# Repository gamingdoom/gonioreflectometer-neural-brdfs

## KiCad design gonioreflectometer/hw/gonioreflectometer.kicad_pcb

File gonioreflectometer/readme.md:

BOM Link: https://docs.google.com/spreadsheets/d/1Ih6BdqQ3d26OCwwXPtMaEUR-iTpFJEZzmPmYw0t3Bok/edit?usp=sharing

Each board contains an RGB led with a TIR lens and a photo diode. They will be connected together in series.
Each board is able to disable/enable the next modules and the ability to program itself in order to facilitate this.

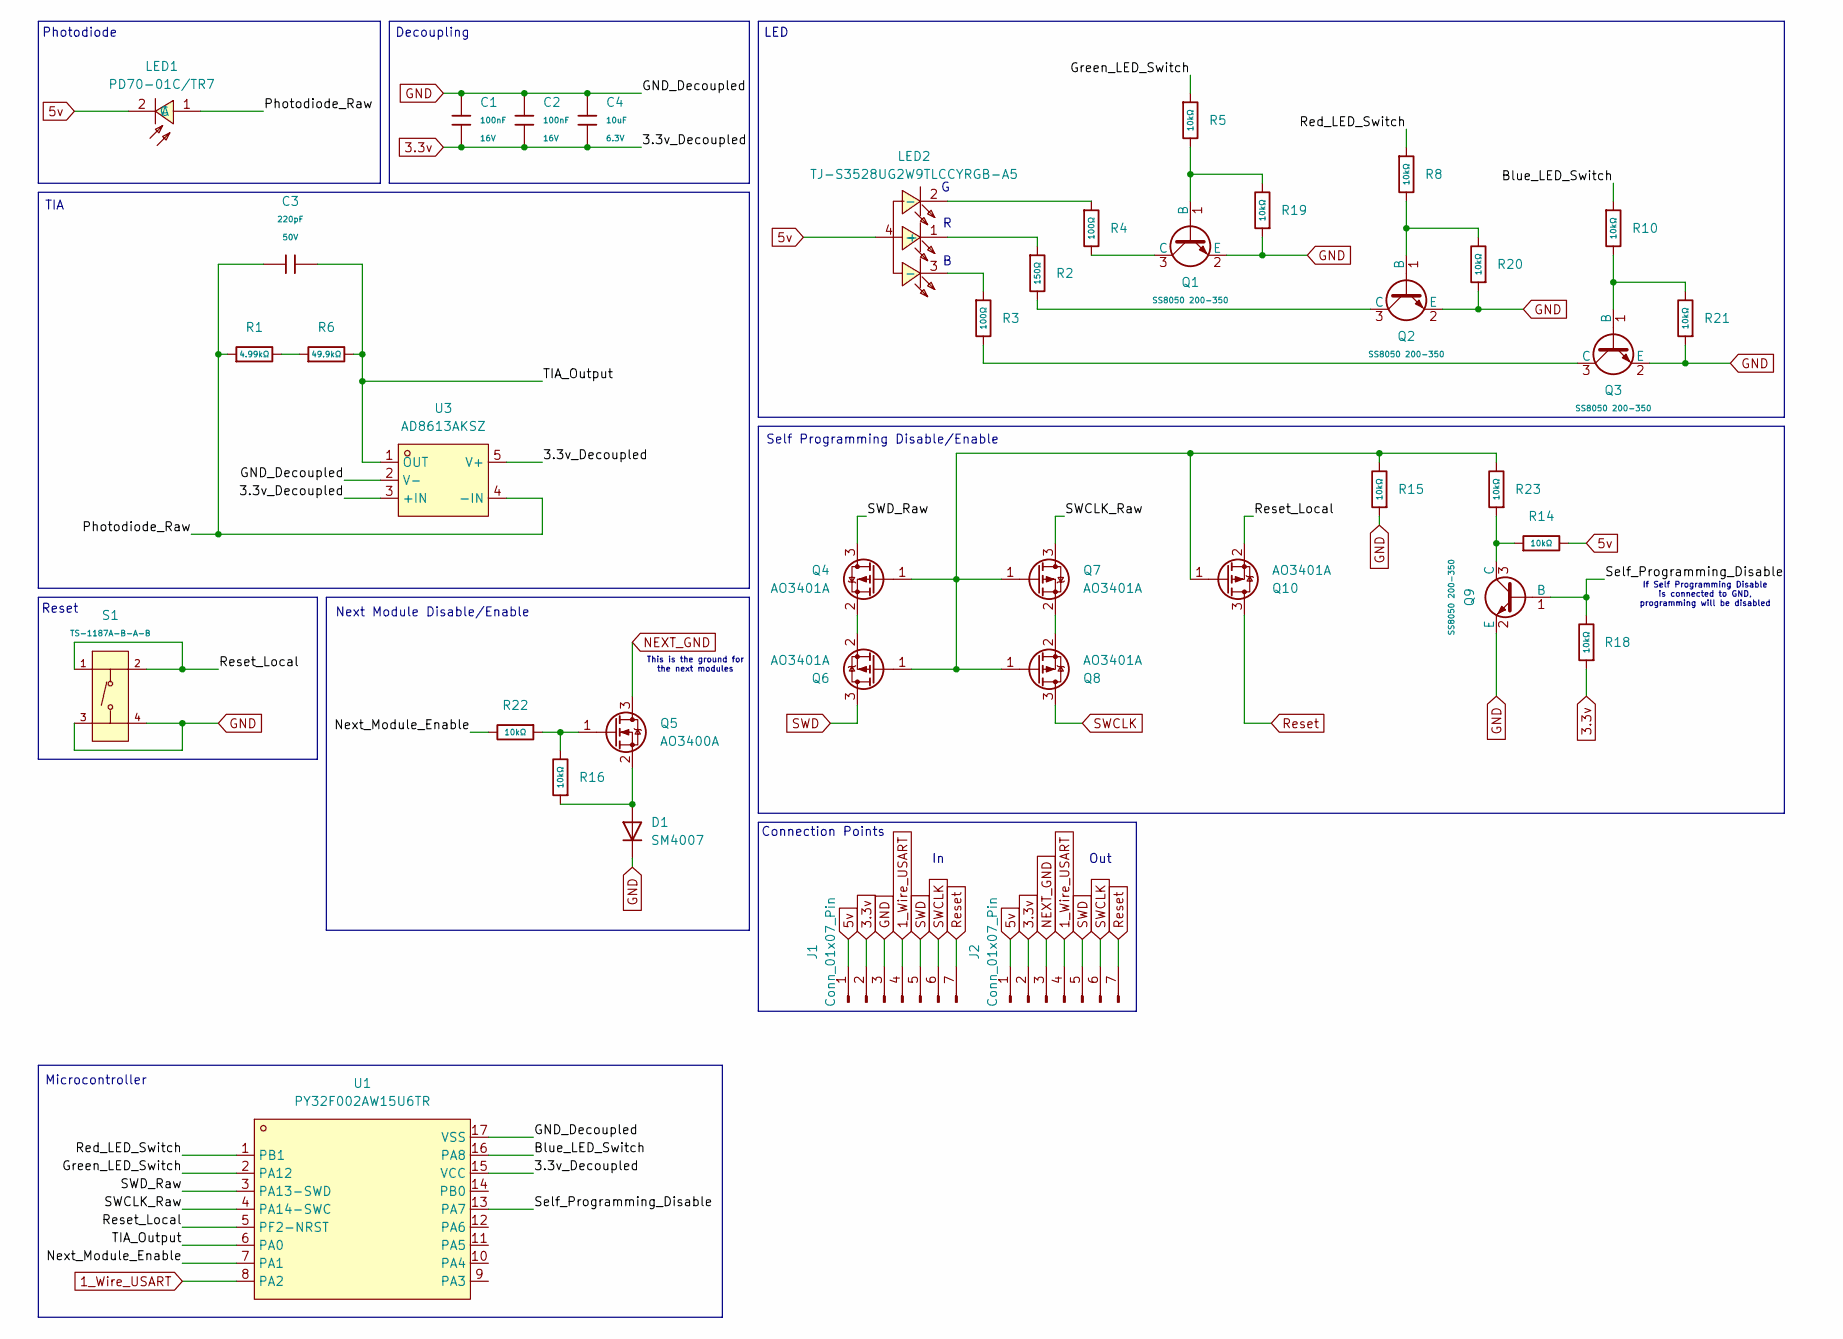
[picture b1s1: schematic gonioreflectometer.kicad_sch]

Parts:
C1, C2: 100nF; C_0402; Voltage Rated 16V; Tolerance ±10%; Part CL05B104KO5NNNC; LCSC C1525
C3: 220pF; C_0402; Voltage Rated 50V; Tolerance ±10%; Part 0402B221K500NT; LCSC C1530
C4: 10uF; C_0402; Voltage Rated 6.3V; Tolerance ±20%; Part CL05A106MQ5NUNC; LCSC C15525
D1: SM4007; D_MELF
J1, J2: Conn_01x07_Pin; PinHeader_1x07_P2.54mm_Vertical
LED1: PD70-01C/TR7; SENSOR-SMD_PD70-01C-TR7; MPN PD70-01C/TR7; LCSC Part C131196
LED2: TJ-S3528UG2W9TLCCYRGB-A5; LED-ARRAY-SMD_4P-L3.2-W2.7-TL-RD_TJ-S3528; MPN TJ-S3528UG2W9TLCCYRGB-A5; LCSC Part C601699
Q1, Q2, Q3, Q9: SS8050 200-350; Q_SOT-23; Part SS8050(RANGE:200-350); LCSC C2150
Q4, Q6, Q7, Q8, Q10: AO3401A; SOT-23
Q5: AO3400A; SOT-23
R1: 4.99kΩ; R_0603; Overload Voltage (Max) 75V; Tolerance ±1%; Part 0603WAF4991T5E; LCSC C23046
R2: 150Ω; R_0603; Overload Voltage (Max) 75V; Tolerance ±1%; Part 0603WAF1500T5E; LCSC C22808
R3, R4: 100Ω; R_0603; Overload Voltage (Max) 75V; Tolerance ±1%; Part 0603WAF1000T5E; LCSC C22775
R5, R8, R10, R14, R15, R16, R18, R19, R20, R21, R22, R23: 10kΩ; R_0402; Overload Voltage (Max) 50V; Tolerance ±1%; Part 0402WGF1002TCE; LCSC C25744
R6: 49.9kΩ; R_0603; Overload Voltage (Max) 75V; Tolerance ±1%; Part 0603WAF4992T5E; LCSC C23184
S1: TS-1187A-B-A-B; SW-SMD_4P-L5.1-W5.1-P3.70-LS6.5-TL-2; Voltage Rating (Dc) 12V; Part TS-1187A-B-A-B; LCSC C318884
U1: PY32F002AW15U6TR; TQFN-16_L3.0-W3.0-P0.50-BL-EP1.7; MPN PY32F002AW15U6TR; LCSC Part C5291740
U3: AD8613AKSZ; SC-70-5_L2.1-W1.3-P0.65-LS2.1-BR; MPN AD8613AKSZ(UMW); LCSC Part C22373372

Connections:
1_Wire_USART: J1.4, J2.4, U1.8 (PA2)
3.3v: C1.2, C2.2, C4.2, J1.2, J2.2, R18.1, U1.15 (VCC), U3.3 (+IN), U3.5 (V+)
5v: J1.1, J2.1, LED1.2 (C), LED2.4 (+), R14.2
/Blue_LED_Switch: R10.1, U1.16 (PA8)
/Green_LED_Switch: R5.1, U1.2 (PA12)
/Next_Module_Enable: R22.2, U1.7 (PA1)
/Photodiode_Raw: C3.1, LED1.1 (A), R1.1, U3.4 (-IN)
/Red_LED_Switch: R8.1, U1.1 (PB1)
/Reset_Local: Q10.2 (S), S1.1 (A), S1.2 (B), U1.5 (PF2-NRST)
/SWCLK_Raw: Q7.3 (D), U1.4 (PA14-SWC)
/SWD_Raw: Q4.3 (D), U1.3 (PA13-SWD)
/Self_Programming_Disable: Q9.1 (B), R18.2, U1.13 (PA7)
/TIA_Output: C3.2, R6.2, U1.6 (PA0), U3.1 (OUT)
GND: C1.1, C2.1, C4.1, D1.1 (K), J1.3, Q1.2 (E), Q2.2 (E), Q3.2 (E), Q9.2 (E), R15.1, R19.1, R20.1, R21.1, S1.3 (C), S1.4 (D), U1.17 (VSS), U3.2 (V-)
NEXT_GND: J2.3, Q5.3 (D)
unnamed: D1.2 (A), Q5.2 (S), R16.1
unnamed: LED2.1 (-), R2.1
unnamed: LED2.2 (-), R4.1
unnamed: LED2.3 (-), R3.1
unnamed: Q1.1 (B), R5.2, R19.2
unnamed: Q1.3 (C), R4.2
unnamed: Q2.1 (B), R8.2, R20.2
unnamed: Q2.3 (C), R2.2
unnamed: Q3.1 (B), R10.2, R21.2
unnamed: Q3.3 (C), R3.2
unnamed: Q4.2 (S), Q6.2 (S)
unnamed: Q5.1 (G), R16.2, R22.1
unnamed: Q7.2 (S), Q8.2 (S)
unnamed: Q9.3 (C), R14.1, R23.1
unnamed: Q4.1 (G), Q6.1 (G), Q7.1 (G), Q8.1 (G), Q10.1 (G), R15.2, R23.2
unnamed: R1.2, R6.1
Reset: J1.7, J2.7, Q10.3 (D)
SWCLK: J1.6, J2.6, Q8.3 (D)
SWD: J1.5, J2.5, Q6.3 (D)

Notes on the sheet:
LED
Next Module Disable/Enable
Microcontroller
Reset
TIA
This is the ground for the next modules
Out
Photodiode
If Self Programming Disable is connected to GND, programming will be disabled
Decoupling
Connection Points
Self Programming Disable/Enable

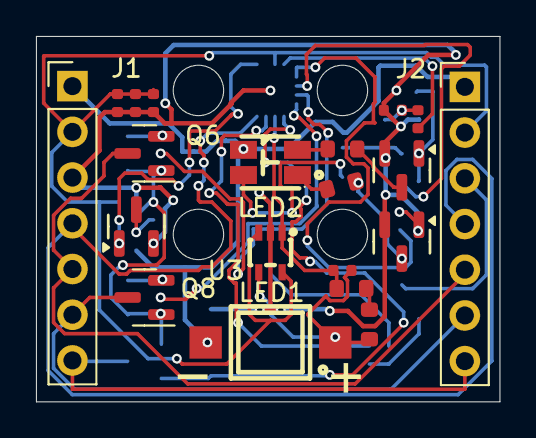
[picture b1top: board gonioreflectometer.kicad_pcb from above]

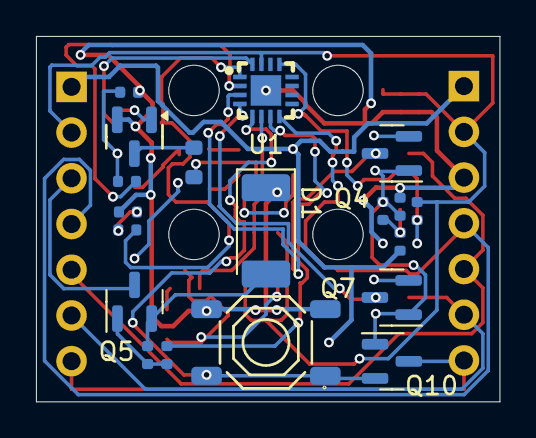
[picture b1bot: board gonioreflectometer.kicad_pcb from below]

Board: 2 copper layers, 25.8 x 20.3 mm, 39 parts (19 on the bottom side), 34 nets.

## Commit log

2026-05-05 Version 1 of Schematic/PCB
2026-05-05 v1.1 compacter (contains drc errors)
2026-05-05 v1.1 fix drc
2026-05-05 v1.1 fix silkscreen on pad
2026-05-05 add more info to readme
2026-05-05 v1.1 minor routing changes
